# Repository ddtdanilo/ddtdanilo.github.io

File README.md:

# Danilo Díaz Tarascó

English-language engineering portfolio and consulting site served as static files from GitHub Pages. Light is the default theme. The theme button saves the visitor’s choice in local storage.

## Edit the site

Update public facts and copy in [data/site.json](data/site.json). The home and consulting pages, case notes, sitemap, Markdown copies and JSON are generated together.

Run python3 tools/build_site.py to regenerate the committed output. Run python3 tools/build_site.py --check to check freshness, privacy patterns, local links and the five legacy redirects. Preview all pages using a static HTTP server from the repository root. Pages serves the committed output without running the generator.

The site assets under assets/css, assets/fonts and assets/img carry the appearance. The generated HTML includes content hashes in linked stylesheet and favicon URLs. The theme and figure scripts and SVG artwork are embedded during generation. Font binaries and licences are recorded in [assets/fonts/LICENSES.md](assets/fonts/LICENSES.md). Swap the logo and favicon with their matching versions. The [home figure](assets/img/path.svg) is a vector illustration of the connected-system stages in [data/path.json](data/path.json). The [plant gateway figure](assets/img/gateway.svg) illustrates the generalized architecture described in the case note. The historical board in the X-Sub note is generated from the [public X-Sub layout](data/xsub/README.md) and includes its licence in the SVG.

Consulting uses the three existing Stripe Payment Links. The return page gives scheduling instructions for buyers. It does not verify a payment. The [privacy page](https://ddtdanilo.github.io/privacy.html) describes site storage and checkout handling. Professional contact is on [LinkedIn](https://www.linkedin.com/in/ddtdanilo/).

The optional Worker under worker/ is separate from the Pages deployment.

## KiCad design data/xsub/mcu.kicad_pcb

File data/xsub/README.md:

# X-Sub board layout

The public [Altium board](https://github.com/X-Sub/Telemetry-System/blob/22aa3054668b9ac26f78241831455f62f9df0d27/PCB/X-Sub_Board/MCU.PcbDoc) was imported with KiCad 10. The original layout and this copy are distributed under the included [MIT license](LICENSE).

```sh
kicad-cli pcb import --format altium -o data/xsub/mcu.kicad_pcb Telemetry-System/PCB/X-Sub_Board/MCU.PcbDoc
python3 tools/build_site.py
python3 tools/build_site.py --check
```

The site generator reads the imported layout with the Python standard library. It writes `assets/img/xsub-board.svg` and `assets/img/board.json`, and inlines the geometry on the X-Sub case note as early work from 2015–2016. The JSON retains exact dimensions. Displayed dimensions are rounded to one decimal place.

The figure shows the original traces, pads, vias, outline, and simplified copper pours. It retains board-level silkscreen outlines. Solder paste, solder mask, fabrication marks, and tiny reference text are omitted. Layer spacing and visible edge thickness illustrate the stack.

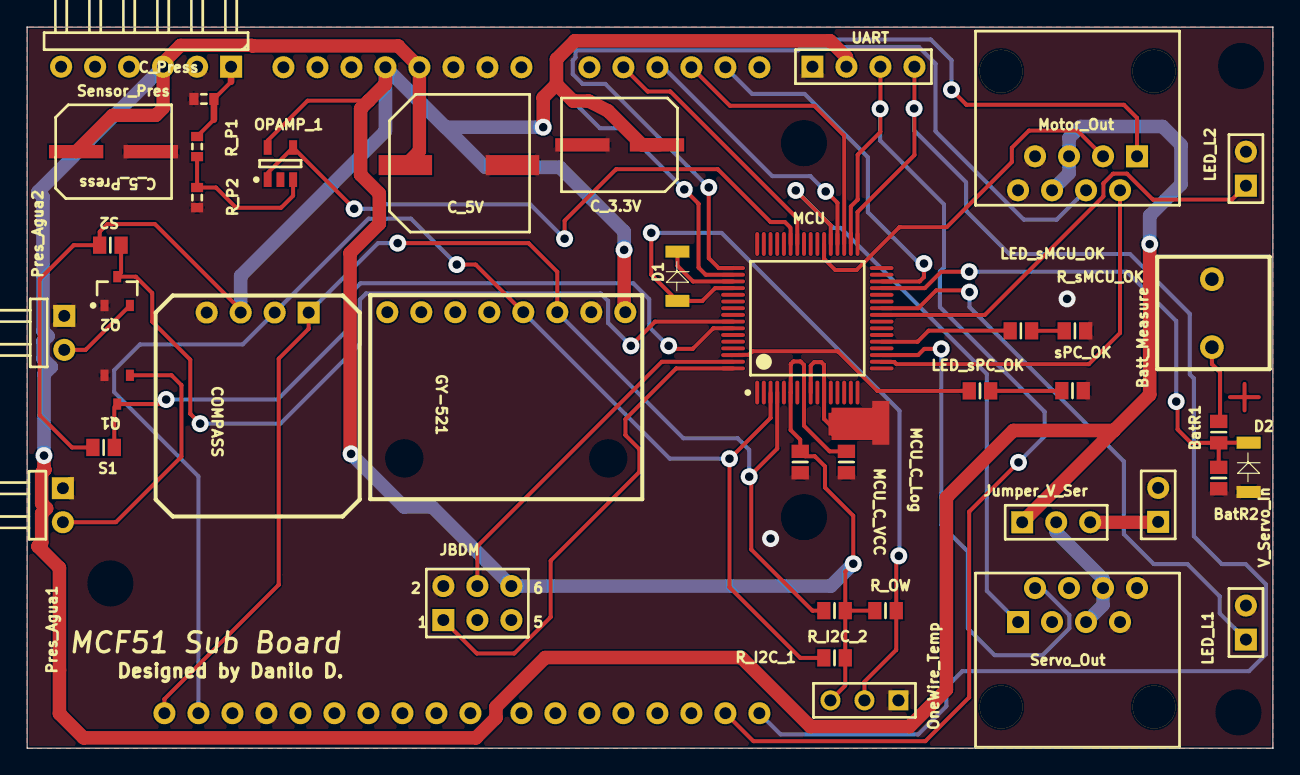
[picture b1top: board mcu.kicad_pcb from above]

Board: 2 copper layers, 93.1 x 53.9 mm, 41 parts (1 on the bottom side), 38 nets.

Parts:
BatR1, BatR2: Res; 6-0805_L
Batt_Measure: Header Batt_M; 5.08mm 200 mil Screw Terminal SF
COMPASS: HMC6352; HMC6352_SF
C_3.3V, C_5_Press: Cap Pol1; Capacitor S Panasonic
C_5V: 330C; C Panasonic Size Cap Pol
C_Press: Cap; J1-0603
D1: Diode 1N4148; miniMELF
D2: Diode Zenner 3.3V; miniMELF
Duino Conn: UNO_R3_SHIELD_NOLABELS
GY-521: MPU-6050 Board GY-521; GY-521
JBDM: Header 3X2; HDR2X3
Jumper_V_Ser: Header 3; HDR1X3
LED_L1: Header 1; HDR1X2
LED_L2: Header 2; HDR1X2
LED_sMCU_OK: LED; 6-0805_L
LED_sPC_OK: LED; 6-0805_L
MCU: MCF51QE128CLH; 840F-02_N
MCU_C_Log: Cap Pol1; 6-0805_L
MCU_C_VCC: Cap Pol1; 6-0805_L
Motor_Out: RJ45-8
OPAMP_1: OPA345NA/250; TI-DBV5_N
OneWire_Temp: HDR1X3
Pres_Agua1, Pres_Agua2: Jumper_STANDAR; HDR1X2H
Q1, Q2: PNP; SOT-23B_L
R_I2C_1, R_I2C_2: Res3; 6-0805_L
R_OW: Res; 6-0805_L
R_P1, R_P2: Res3; J1-0603
R_sMCU_OK: Res; 6-0805_L
S1, S2: Res; 6-0805_L
Sensor_Pres: MPX5700AP; HDR1X6H
Servo_Out: RJ45-8
UART: Header 4; HDR1X4
V_Servo_In: Header 2; HDR1X2
sPC_OK: Res; 6-0805_L

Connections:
+3.3V: COMPASS.3, C_3.3V.1, Duino Conn.3.3V, GY-521.1, JBDM.6, MCU.6, MCU.8, MCU_C_Log.1, MCU_C_VCC.1, OPAMP_1.5, OneWire_Temp.3, R_I2C_1.2, R_I2C_2.2, R_OW.2, S1.2, S2.2, UART.2
+5V: C_5V.1, C_5_Press.1, Duino Conn.5V, Jumper_V_Ser.1, Motor_Out.5, Motor_Out.6, Sensor_Pres.3
+V_SERVO: Jumper_V_Ser.3, V_Servo_In.1
+V_SERVO_IN: Jumper_V_Ser.2, Servo_Out.5, Servo_Out.6
AD1: Duino Conn.A1, MCU.42
AD2: Duino Conn.A2, MCU.36
AD3: Duino Conn.A3, MCU.35
AD4: Duino Conn.A4, MCU.30
AD5_BAT: BatR1.1, BatR2.2, D2.2, MCU.29
ADC_PRESSURE_3.3V: MCU.43, OPAMP_1.1, OPAMP_1.4
BKGD: JBDM.1, MCU.64
GND: BatR2.1, Batt_Measure.1, COMPASS.4, C_3.3V.2, C_5V.2, C_5_Press.2, C_Press.1, D2.1, Duino Conn.GND@0, Duino Conn.GND@1, Duino Conn.GND@2, GY-521.2, JBDM.2, LED_L1.2, LED_L2.2, MCU.9, MCU.11, MCU_C_Log.2, MCU_C_VCC.2, Motor_Out.7, Motor_Out.8, OPAMP_1.2, OneWire_Temp.1, Pres_Agua1.1, Pres_Agua2.1, Q1.1, Q2.1, R_P2.1, R_sMCU_OK.1, Sensor_Pres.2, Servo_Out.7, Servo_Out.8, UART.1, V_Servo_In.2, sPC_OK.1
LEDLIGHT1: LED_L1.1, MCU.26
LEDLIGHT2: LED_L2.1, MCU.25
M1_ESC: MCU.50, Motor_Out.1
M2_ESC: MCU.18, Motor_Out.2
M3_ESC: MCU.38, Motor_Out.3
M4_ESC: MCU.49, Motor_Out.4
NetBatR1_2: BatR1.2, Batt_Measure.2
NetLED_sMCU_OK_2: LED_sMCU_OK.2, R_sMCU_OK.2
NetLED_sPC_OK_2: LED_sPC_OK.2, sPC_OK.2
NetOPAMP_1_3: OPAMP_1.3, R_P1.1, R_P2.2
NetPres_Agua1_2: Pres_Agua1.2, Q1.2
NetPres_Agua2_2: Pres_Agua2.2, Q2.2
PRESENCIAAGUA1: MCU.58, Q1.3, S1.1
PRESENCIAAGUA2: MCU.57, Q2.3, S2.1
P_OUT: C_Press.2, R_P1.2, Sensor_Pres.1
RESET: JBDM.4, MCU.63
RXSERIALCOM: Duino Conn.TX, MCU.34, UART.3
RXSERIALCOM2: D1.1, MCU.52, OneWire_Temp.2, R_OW.1
SCL: COMPASS.1, Duino Conn.SCL, GY-521.3, MCU.4, R_I2C_2.1
SDA: COMPASS.2, Duino Conn.SDA, GY-521.4, MCU.3, R_I2C_1.1
SMCU_OK: LED_sMCU_OK.1, MCU.21
SPC_OK: LED_sPC_OK.1, MCU.62
S_PANCAMERA: MCU.19, Servo_Out.2
S_TILTCAMERA: MCU.37, Servo_Out.1
TXSERIALCOM: Duino Conn.RX, MCU.33, UART.4
TXSERIALCOM2: D1.2, MCU.51
